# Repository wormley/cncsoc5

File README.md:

# cncsoc5
Off-board CNC for PSoC 5LP CYC8KIT-059

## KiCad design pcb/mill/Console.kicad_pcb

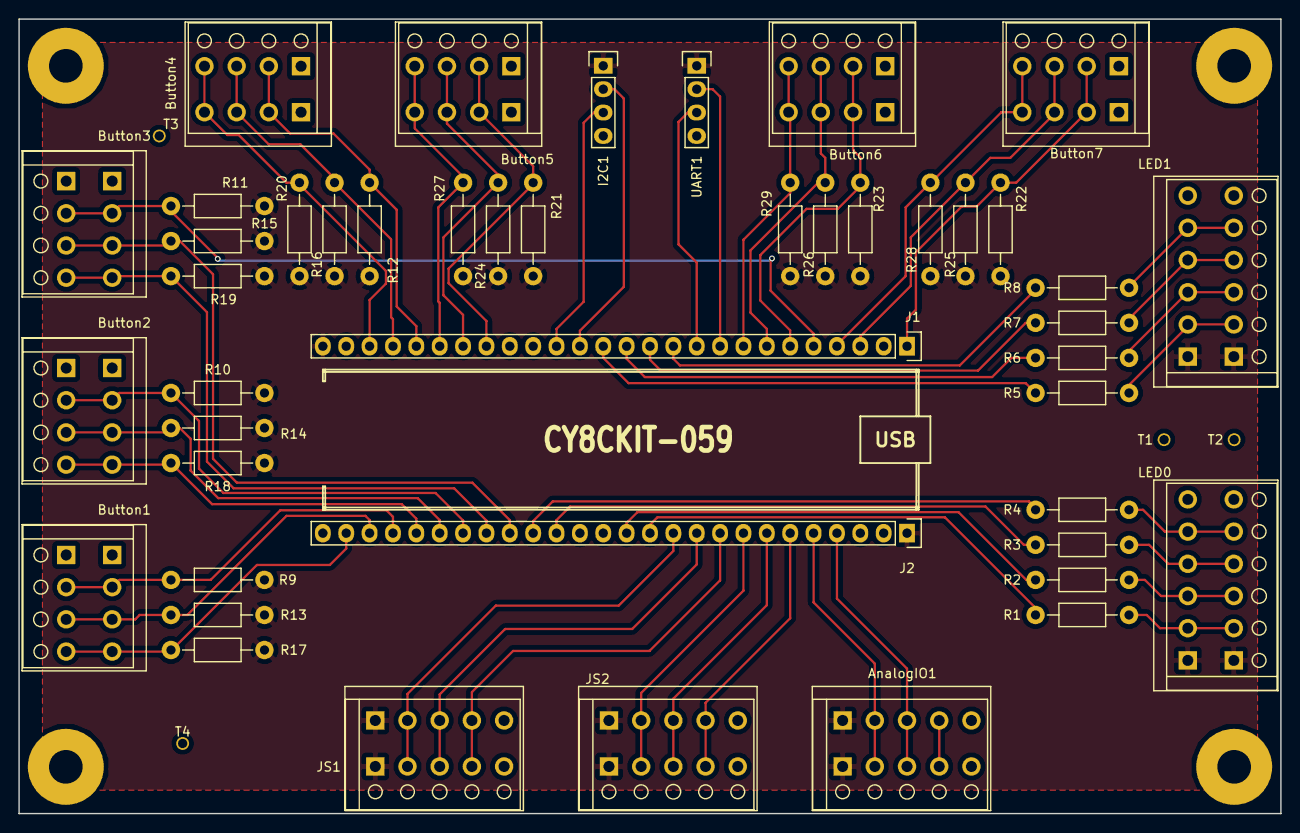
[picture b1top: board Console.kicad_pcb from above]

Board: 2 copper layers, 137.2 x 86.4 mm, 53 parts (0 on the bottom side), 51 nets.

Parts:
AnalogIO1: CONN_01X05; PTSA-5
B1, B2, B3, B4: HOLE; MH-No6-3p5
Button1, Button2, Button3, Button4, Button5, Button6, Button7: CONN_01X04; PTSA-4
I2C1: CONN_01X04; Pin_Header_Straight_1x04
J1, J2: CONN_01X26; Pin_Header_Straight_1x26
JS1, JS2: CONN_01X05; PTSA-5
LED0, LED1: CONN_01X06; PTSA-6
R1, R2, R3, R4, R5, R6, R7, R8: 330; Resistor_Horizontal_RM10mm
R9, R10, R11, R12, R13, R14, R15, R16, R17, R18, R19, R20, R21, R22, R23, R24, R25, R26, R27, R28, R29: 4.7K; Resistor_Horizontal_RM10mm
T1, T2, T3, T4: TP; TP-TH
UART1: CONN_01X04; Pin_Header_Straight_1x04

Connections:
/GND: AnalogIO1.5, Button1.1, Button2.1, Button3.1, Button4.1, Button5.1, Button6.1, Button7.1, I2C1.4, J1.25, J2.2, J2.26, JS1.5, JS2.5, LED0.6, LED1.6, T1.1, T2.1, T3.1, T4.1, UART1.4
/P0.0: J2.11, JS1.2
/P0.1: J2.10, JS1.3
/P0.2: J2.9, JS1.4
/P0.3: J2.8, JS2.2
/P0.4: J2.7, JS2.3
/P0.5: J2.6, JS2.4
/P0.6: AnalogIO1.2, J2.5
/P0.7: AnalogIO1.3, J2.4
/P1.2: Button5.2, J1.19, R21.2
/P1.3: Button5.3, J1.20, R24.2
/P1.4: Button5.4, J1.21, R27.2
/P1.5: Button4.2, J1.22, R12.2
/P1.6: Button4.3, J1.23, R16.2
/P1.7: Button4.4, J1.24, R20.2
/P2.0: Button7.2, J1.1, R22.2
/P2.2: Button7.3, J1.3, R25.2
/P2.3: Button7.4, J1.4, R28.2
/P2.4: Button3.2, J1.5, R11.2
/P2.5: Button6.2, J1.6, R23.2
/P2.6: Button6.3, J1.7, R26.2
/P2.7: Button6.4, J1.8, R29.2
/P3.0: Button1.4, J2.25, R17.2
/P3.1: Button1.3, J2.24, R13.2
/P3.2: Button1.2, J2.23, R9.2
/P3.3: Button2.4, J2.22, R18.2
/P3.4: Button2.3, J2.21, R14.2
/P3.5: Button2.2, J2.20, R10.2
/P3.6: Button3.4, J2.19, R19.2
/P3.7: Button3.3, J2.18, R15.2
/P12.2: J1.14, R5.1
/P12.3: J1.13, R6.1
/P12.4: J1.12, R7.1
/P12.5: J1.11, R8.1
/P15.0: J2.17, R4.1
/P15.1: J2.16, R3.1
/P15.4: J2.13, R2.1
/P15.5: J2.12, R1.1
/RCV: J1.10, UART1.3
/SCL: I2C1.3, J1.16
/SDA: I2C1.2, J1.15
/TXD: J1.9, UART1.2
/VDD: AnalogIO1.1, I2C1.1, J1.26, J2.1, JS1.1, JS2.1, LED0.1, LED1.1, R9.1, R10.1, R11.1, R12.1, R13.1, R14.1, R15.1, R16.1, R17.1, R18.1, R19.1, R20.1, R21.1, R22.1, R23.1, R24.1, R25.1, R26.1, R27.1, R28.1, R29.1, UART1.1
unnamed: LED0.2, R1.2
unnamed: LED0.3, R2.2
unnamed: LED0.4, R3.2
unnamed: LED0.5, R4.2
unnamed: LED1.2, R5.2
unnamed: LED1.3, R6.2
unnamed: LED1.4, R7.2
unnamed: LED1.5, R8.2

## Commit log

2018-12-04 Initial Setup
2019-01-21 PCB update
